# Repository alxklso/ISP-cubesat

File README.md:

# ISP-cubesat
This is the repo for the Isomer Space Program (ISP) 1U CoyoteSat CubeSat mission.

This repo contains:
- [mainboard-v05]: PyCubed V5 Mainboard  
- [batt-board]: PyCubed V1b Battery Board
- [software]: PyCubed Flight Software  
- [cosmic-watch]: Cosmic Watch (payload)
- [solar-panels]: Solar Panel PCBs
- [antenna]: Antenna PCBs
- [bottom-adapter]: Bottom adapter plate w/ solar cells
- [ISP.pretty]: Custom KiCad footprint library
- [datasheets]: Datasheets for components 
- [firmware]: Firmware for PyCubed V5 board
- [pics]: Progress pics of the CubeSat

Visit our website to learn more: [ISP Website](https://isomer.space)

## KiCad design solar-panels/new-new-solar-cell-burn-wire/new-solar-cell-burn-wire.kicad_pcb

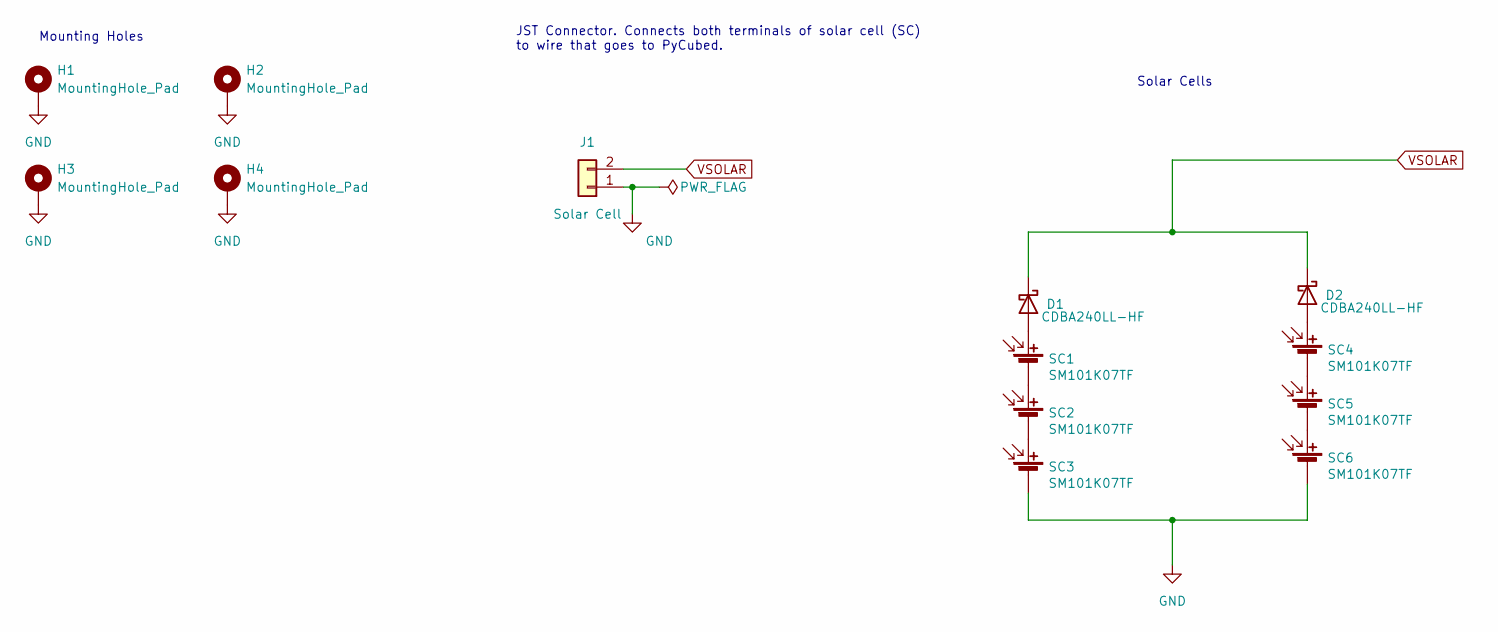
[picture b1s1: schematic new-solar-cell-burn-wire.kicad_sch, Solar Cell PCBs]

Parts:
D1, D2: CDBA240LL-HF; DO-214AC
H1, H2, H3, H4: MountingHole_Pad; MountingHole_3.2mm_M3_DIN965_Pad
J1: Solar Cell; 2053380002
SC1, SC2, SC3, SC4, SC5, SC6: SM101K07TF

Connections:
GND: H1.1, H2.1, H3.1, H4.1, J1.1, SC3.2 (-), SC6.2 (-)
unnamed: D1.2 (A), SC1.1 (+)
unnamed: D2.2 (A), SC4.1 (+)
unnamed: SC1.2 (-), SC2.1 (+)
unnamed: SC2.2 (-), SC3.1 (+)
unnamed: SC4.2 (-), SC5.1 (+)
unnamed: SC5.2 (-), SC6.1 (+)
VSOLAR: D1.1 (K), D2.1 (K), J1.2

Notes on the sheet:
Mounting Holes
Solar Cells
JST Connector. Connects both terminals of solar cell (SC) to wire that goes to PyCubed.

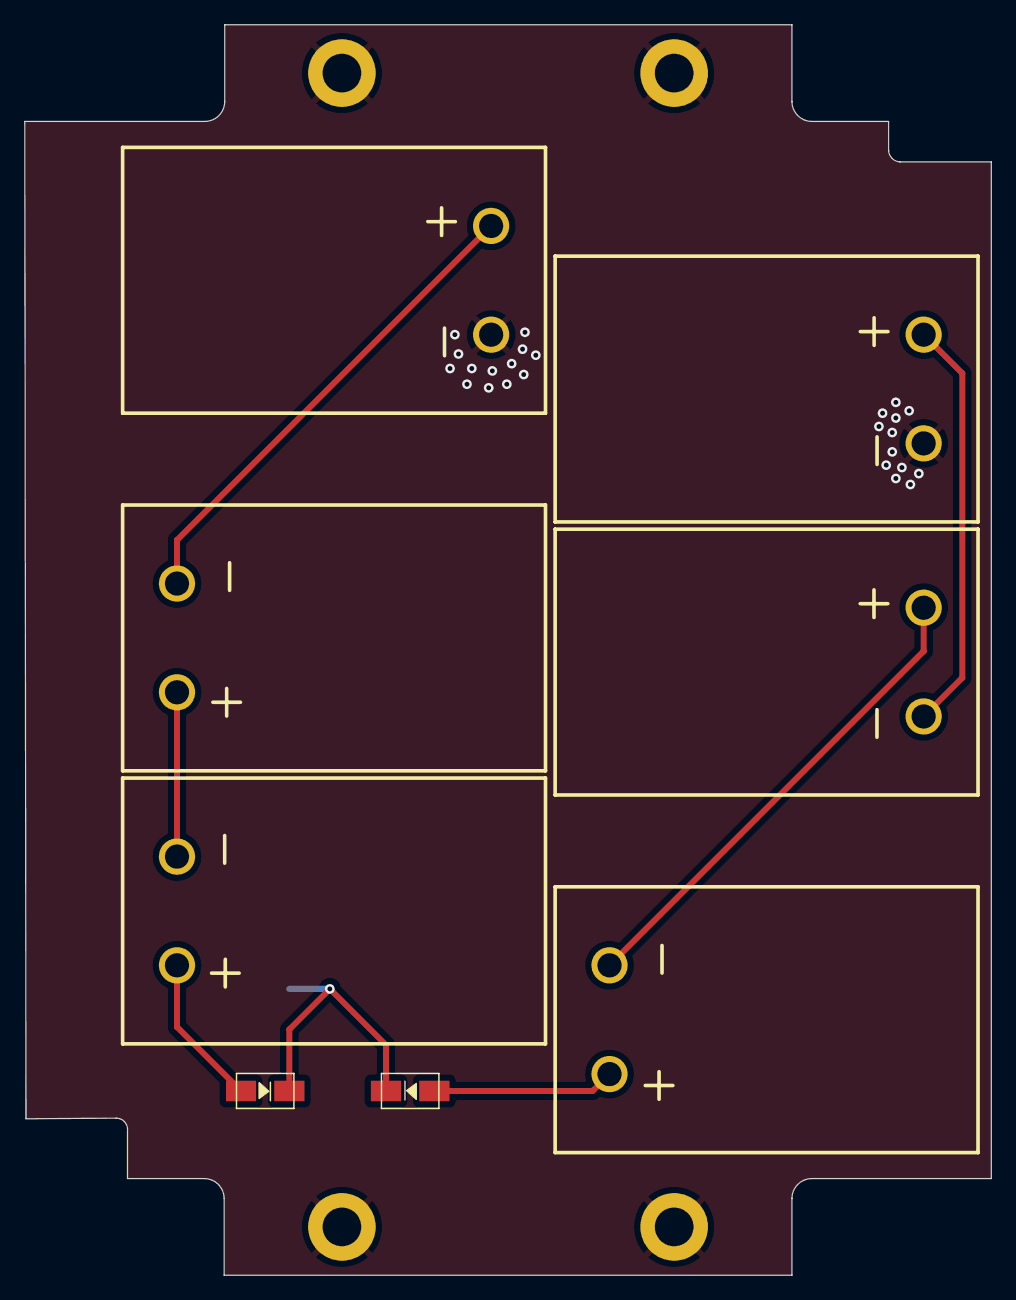
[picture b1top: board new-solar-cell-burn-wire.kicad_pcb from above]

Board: 2 copper layers, 80.0 x 103.5 mm, 13 parts (1 on the bottom side), 8 nets.

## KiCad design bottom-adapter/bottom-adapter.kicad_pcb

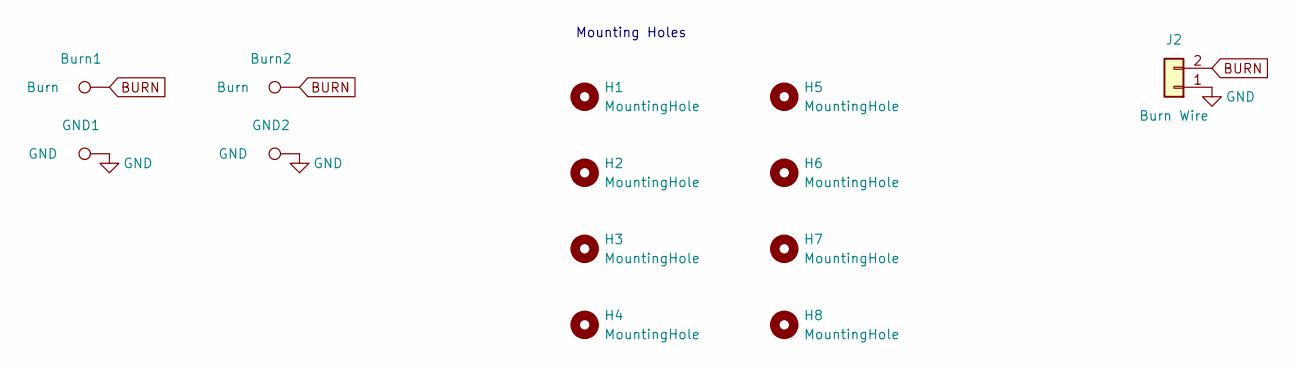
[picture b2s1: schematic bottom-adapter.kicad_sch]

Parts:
Burn1, Burn2: Burn; TestPoint_THTPad_2.0x2.0mm_Drill1.0mm
GND1, GND2: GND; TestPoint_THTPad_2.0x2.0mm_Drill1.0mm
H1, H2, H3, H4: MountingHole; MountingHole_3.7mm_Pad_Modified
H5, H6, H7, H8: MountingHole; MountingHole_2.7mm_M2.5_DIN965_Pad
J2: Burn Wire; pico_lock_2mm_2circuit

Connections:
BURN: Burn1.1, Burn2.1, J2.2
GND: GND1.1, GND2.1, J2.1

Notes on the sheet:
Mounting Holes

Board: 2 copper layers, 14 parts (1 on the bottom side), 2 nets, no tracks yet.

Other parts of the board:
G: LOGO

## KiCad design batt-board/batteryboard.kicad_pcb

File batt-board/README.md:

# PyCubed Battery Board 🔋

## [⭐ See the PyCubed Battery page for more details](https://www.notion.so/maholli/PyCubed-4cbfac7e9b684852a2ab2193bd485c4d)

2S2P Li-ion battery pack for CubeSat designs.
   - Fits 18650 cells (like the LG INR18650-MJ1)
   - Meets maximum capacity requirements of common CubeSat integrators
   - Uses components with radiation testing heritage
      - R5460x2xx for protection against
         - over-charge 
         - over-discharge
         - short-circuit
         - excess discharge-current
         - excess charge-current

## Interactive Bill of Materials 🛒
- [batteryboard-v01](https://pycubed.github.io/hardware/batteryboard-v01)

This board is merely a starting point for your spacecraft. Always follow the requirements set forth by your launch provider and integrator.

<br>
<br>
<br>
<br />This work is licensed under a <a rel="license" href="http://creativecommons.org/licenses/by/4.0/">Creative Commons Attribution 4.0 International License</a>.

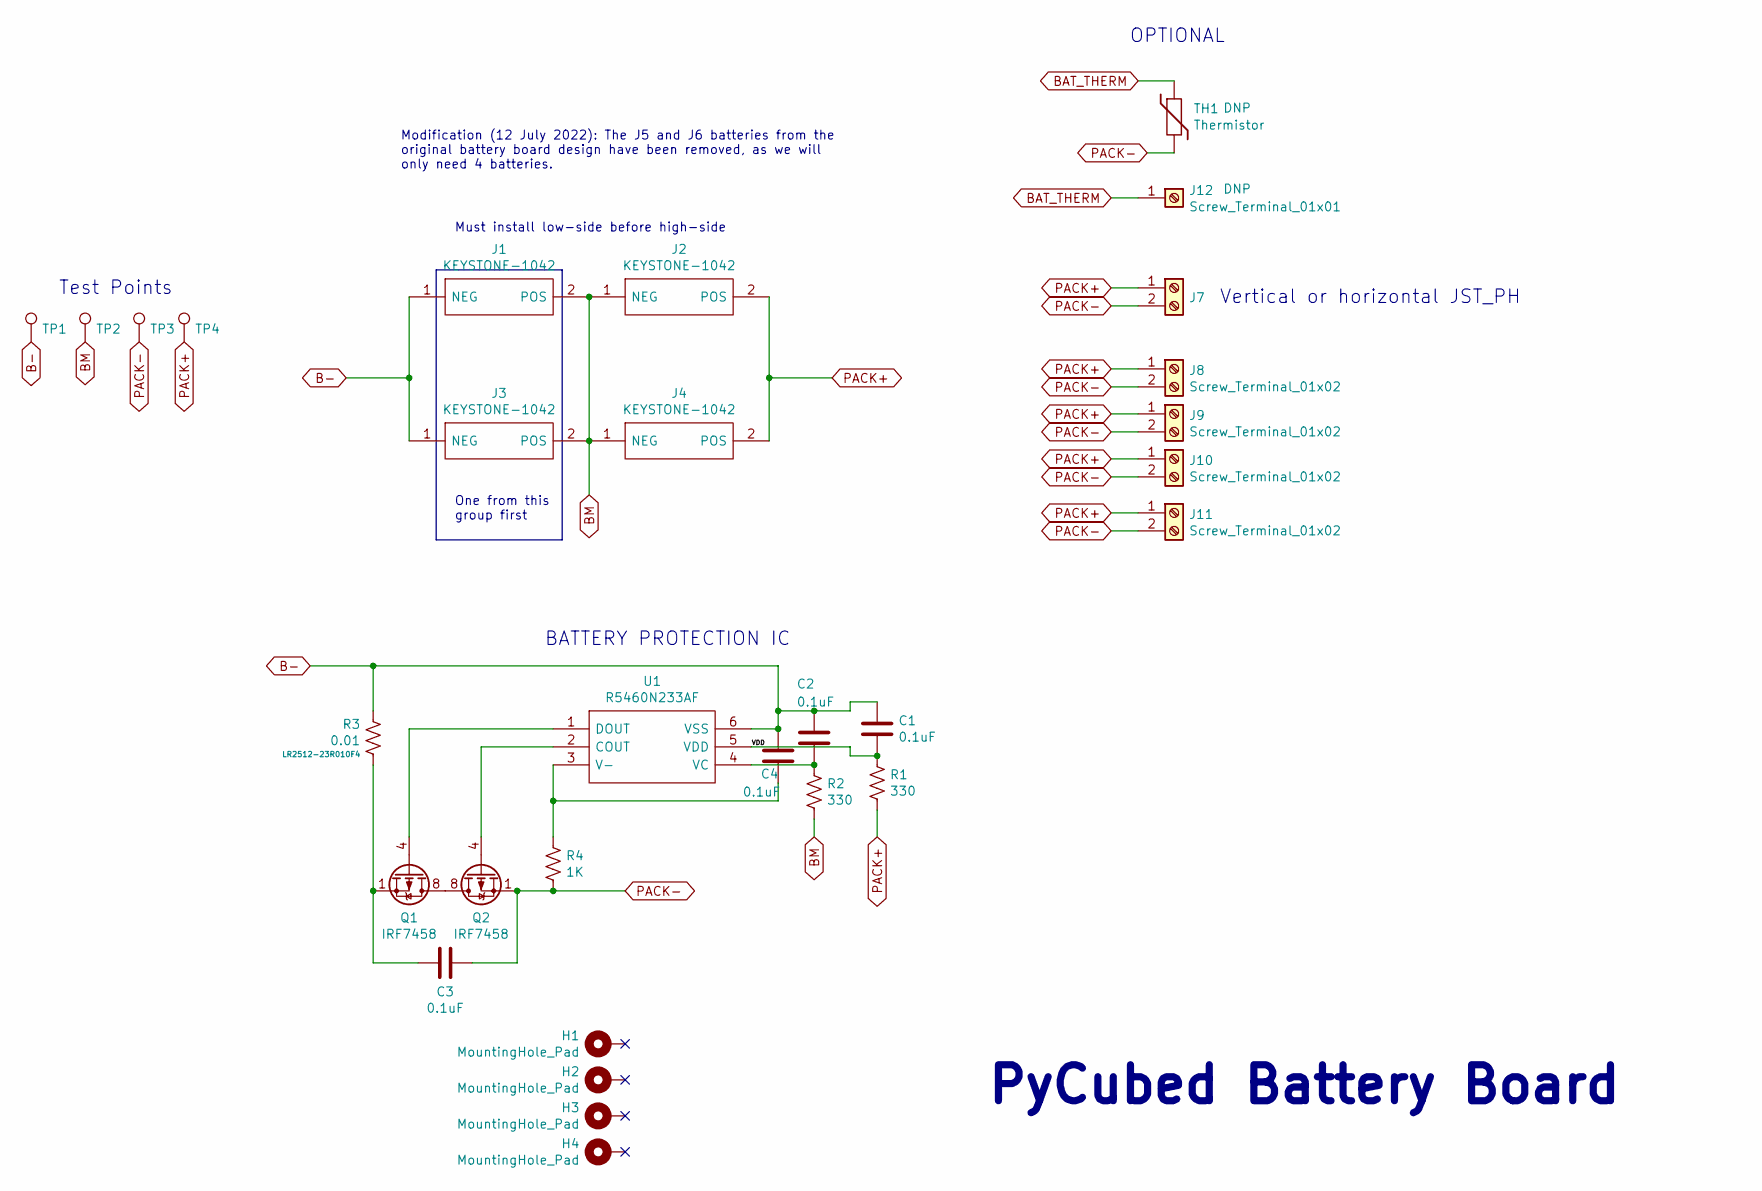
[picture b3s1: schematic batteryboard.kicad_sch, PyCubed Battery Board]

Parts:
C1, C2, C3, C4: 0.1uF; C_0603_1608Metric
H1, H2, H3, H4: MountingHole_Pad; MountingHole_3.2mm_M3_DIN965_PadMOD
J1, J2, J3, J4: KEYSTONE-1042; Manufacturer_Part_Number 1042; Mouser Part Number 534-1042
J7: JST_PH_S2B-PH-SM4; JST_PH_S2B-PH-SM4-TB_1x02-1MP_P2.00mm_Horizontal
J8, J9, J10, J11: Screw_Terminal_01x02; SCREWTERMINAL-3.5MM-2_LOCK
J12: Screw_Terminal_01x01; PinHeader_1x01_P1.00mm_Vertical
Q1, Q2: IRF7458; SOIC-8_3.9x4.9mm_P1.27mm
R1, R2: 330; R_0603_1608Metric
R3: 0.01; R_2512_6332Metric
R4: 1K; R_0603_1608Metric; Manufacturer_Part_Number LR2512-23R010F4
TH1: Thermistor; R_Axial_DIN0204_L3.6mm_D1.6mm_P5.08mm_Vertical
TP1, TP2, TP3, TP4: TestPoint; TestPoint_Loop_D1.80mm_Drill1.0mm_Beaded
U1: R5460N233AF; SOT95P280X130-6N; Manufacturer_Part_Number R5460N233AF-TR-FE; Mouser Part Number 848-R5460N233AFTRFE

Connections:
/VDD: C1.2, R1.2, U1.5 (VDD)
B-: C1.1, C2.1, C4.1, J1.1 (NEG), J3.1 (NEG), R3.1, TP1.1, U1.6 (VSS)
BAT_THERM: J12.1, TH1.1
BM: J1.2 (POS), J2.1 (NEG), J3.2 (POS), J4.1 (NEG), R2.1, TP2.1
unnamed: C2.2, R2.2, U1.4 (VC)
unnamed: C3.1, Q1.1 (S), Q1.2 (S), Q1.3 (S), R3.2
unnamed: C4.2, R4.1, U1.3 (V-)
unnamed: Q1.4 (G), U1.1 (DOUT)
unnamed: Q1.5 (D), Q1.6 (D), Q1.7 (D), Q1.8 (D), Q2.5 (D), Q2.6 (D), Q2.7 (D), Q2.8 (D)
unnamed: Q2.4 (G), U1.2 (COUT)
PACK+: J2.2 (POS), J4.2 (POS), J7.1, J8.1, J9.1, J10.1, J11.1, R1.1, TP4.1
PACK-: C3.2, J7.2, J8.2, J9.2, J10.2, J11.2, Q2.1 (S), Q2.2 (S), Q2.3 (S), R4.2, TH1.2, TP3.1

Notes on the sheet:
BATTERY PROTECTION IC
One from this group first
Test Points
Modification (12 July 2022): The J5 and J6 batteries from the original battery board design have been removed, as we will only need 4 batteries.
Must install low-side before high-side
Vertical or horizontal JST_PH
PyCubed Battery Board
OPTIONAL

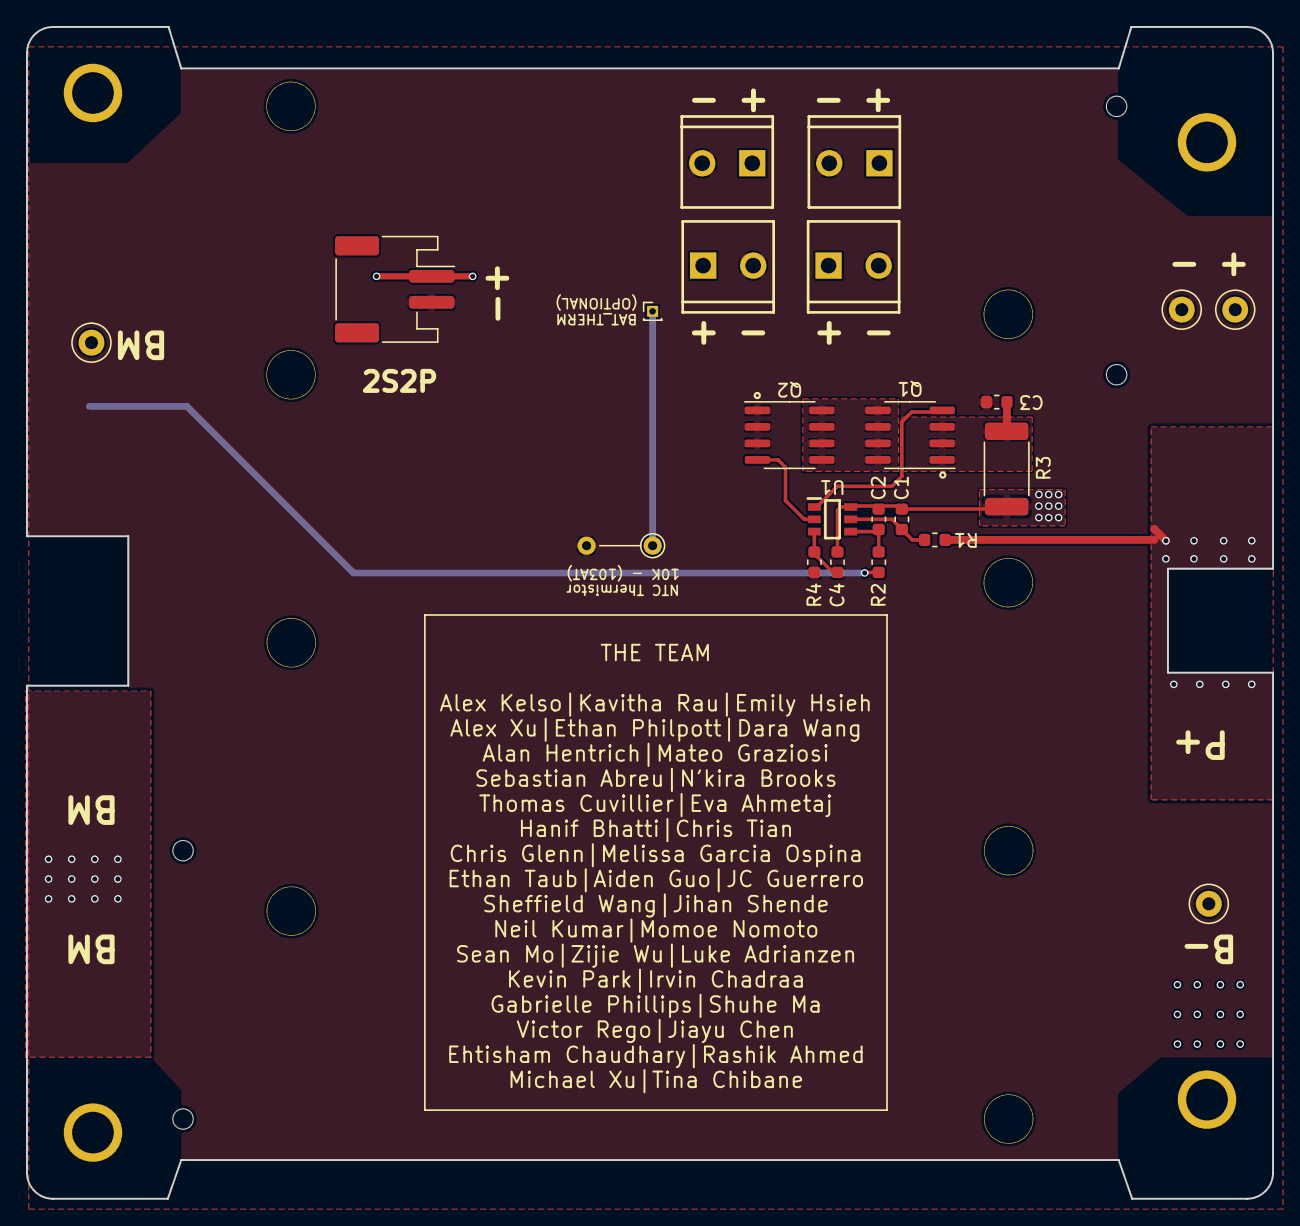
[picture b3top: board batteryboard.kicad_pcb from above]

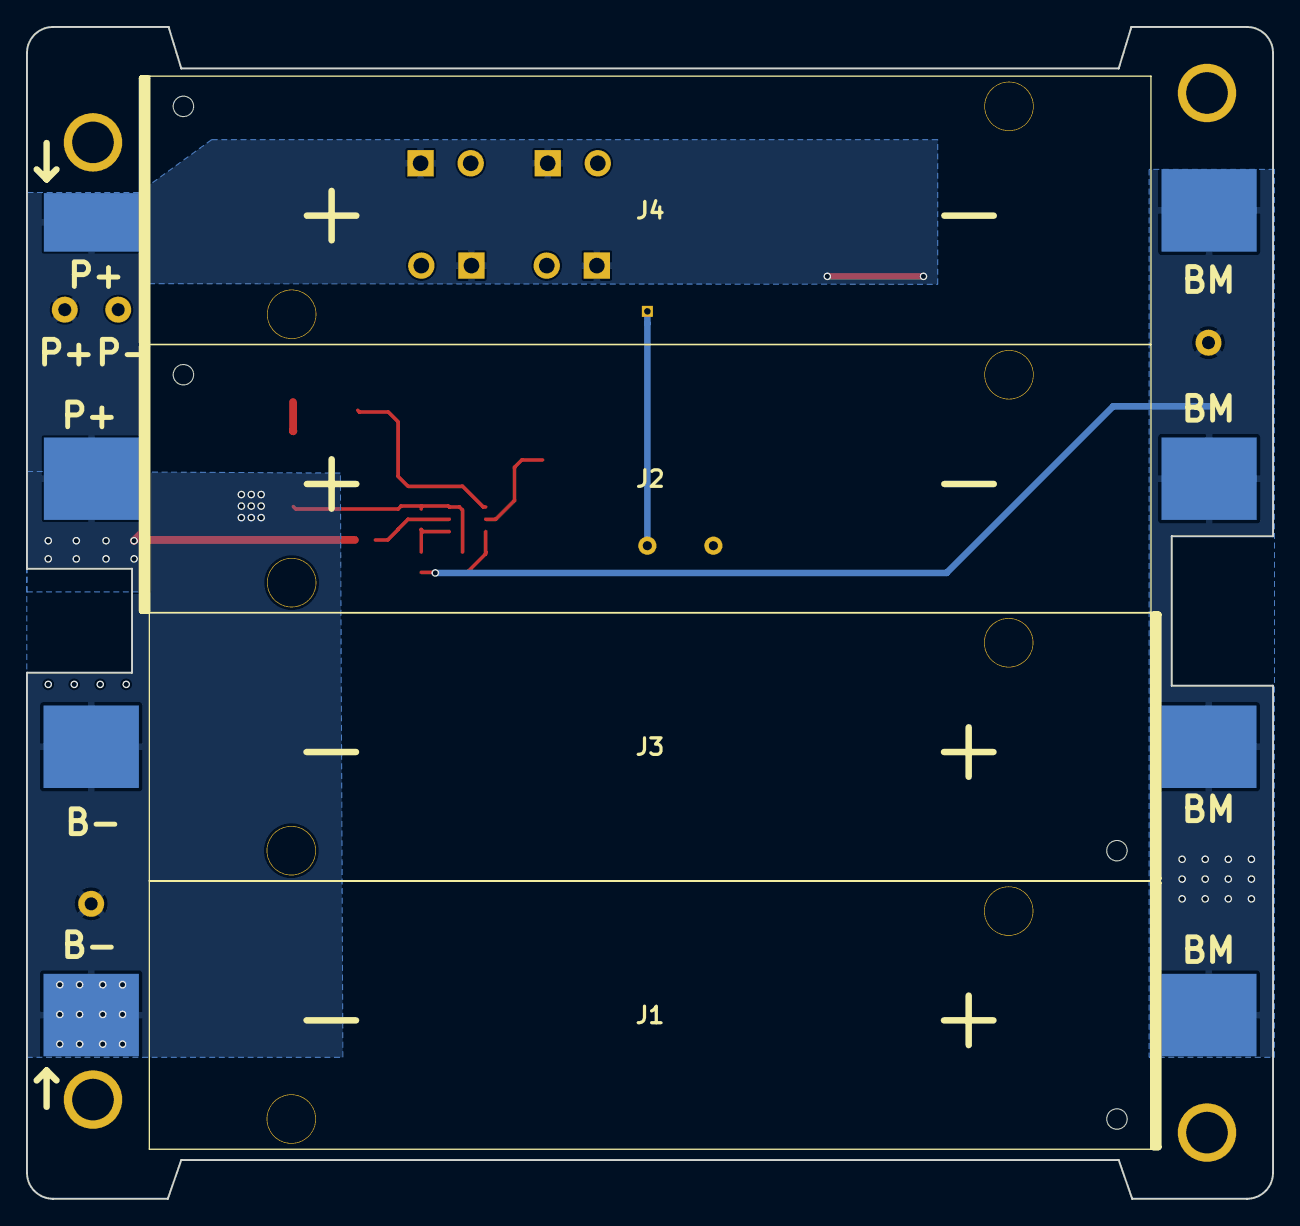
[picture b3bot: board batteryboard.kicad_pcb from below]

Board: 2 copper layers, 95.9 x 90.2 mm, 30 parts (4 on the bottom side), 12 nets.

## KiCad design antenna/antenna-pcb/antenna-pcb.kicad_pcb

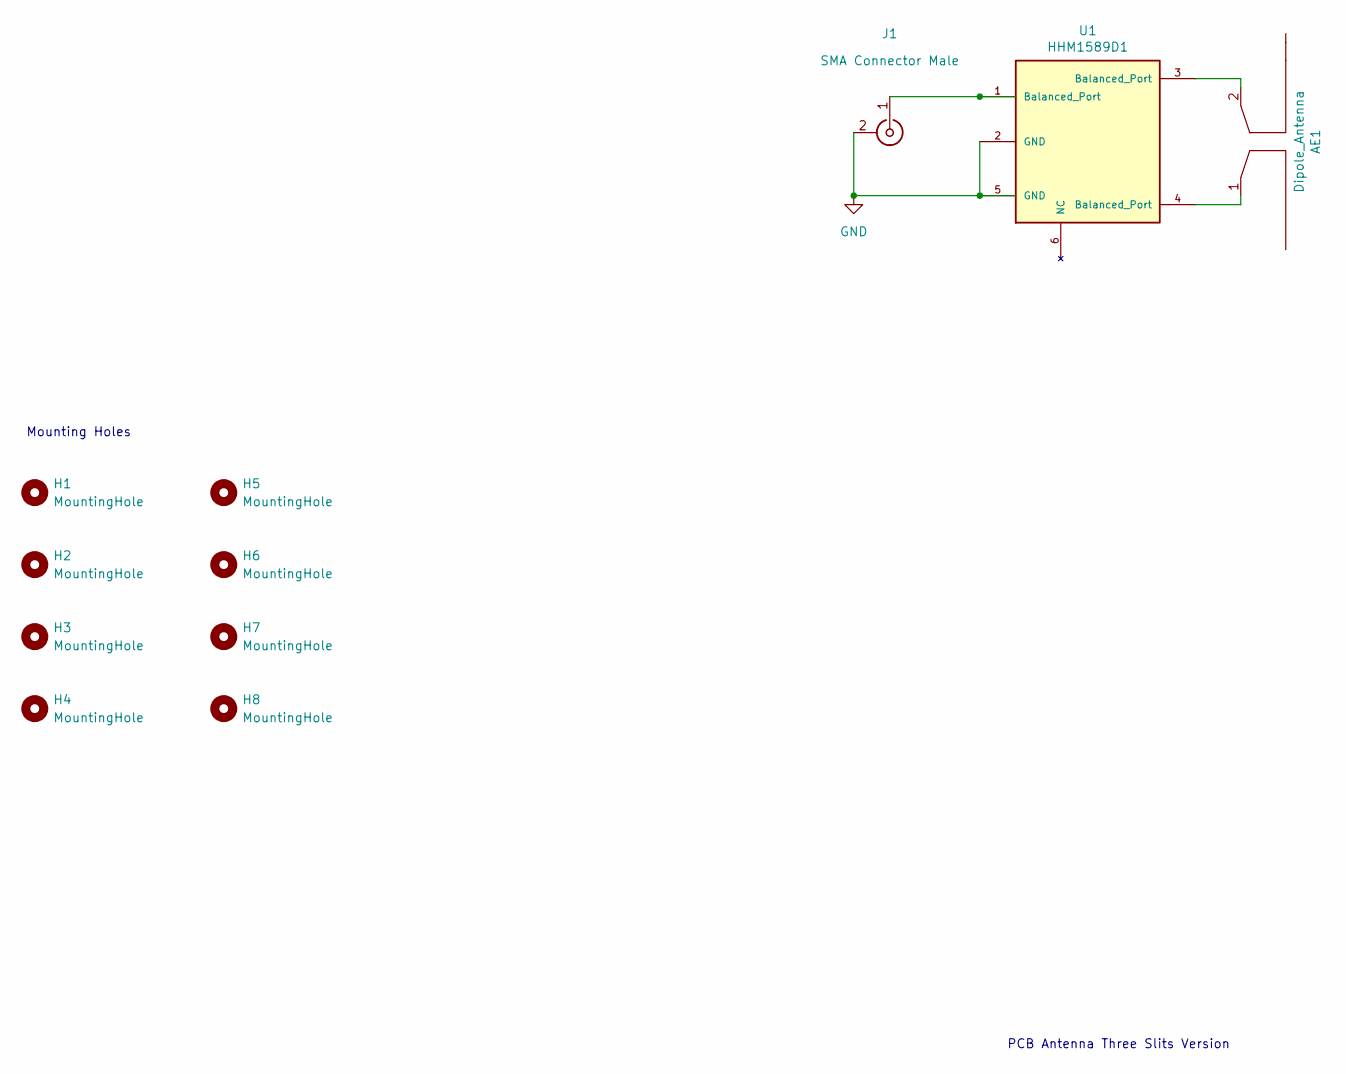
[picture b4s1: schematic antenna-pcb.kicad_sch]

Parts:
AE1: Dipole_Antenna; Antenna_Pads
H1, H2, H3, H4: MountingHole; MountingHole_3.7mm_Pad_Modified
H5, H6, H7, H8: MountingHole; MountingHole_2.7mm_M2.5_DIN965_Pad
J1: SMA Connector Male; SMA_Connector
U1: HHM1589D1; Balun_Johanson_5400BL15B050E

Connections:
GND: J1.2 (Ext), U1.2 (GND), U1.5 (GND)
unnamed: J1.1 (In), U1.1 (Balanced_Port)
unnamed: AE1.2, U1.3 (Balanced_Port)
unnamed: AE1.1, U1.4 (Balanced_Port)

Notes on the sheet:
Mounting Holes
PCB Antenna Three Slits Version

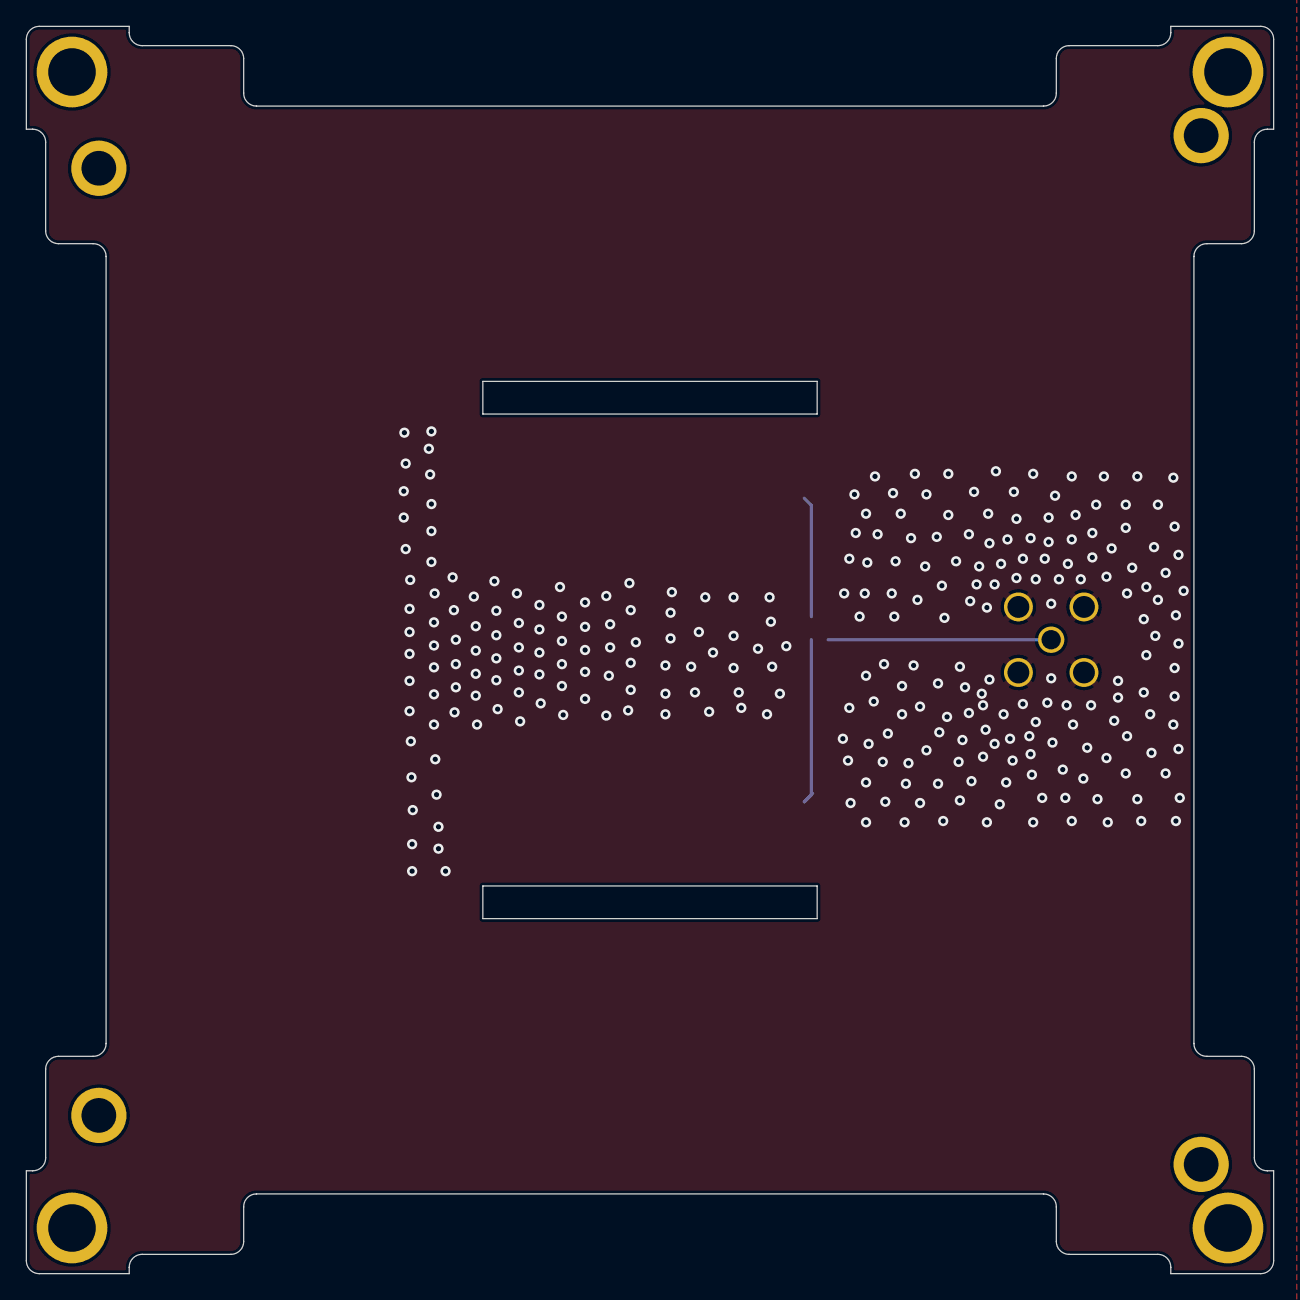
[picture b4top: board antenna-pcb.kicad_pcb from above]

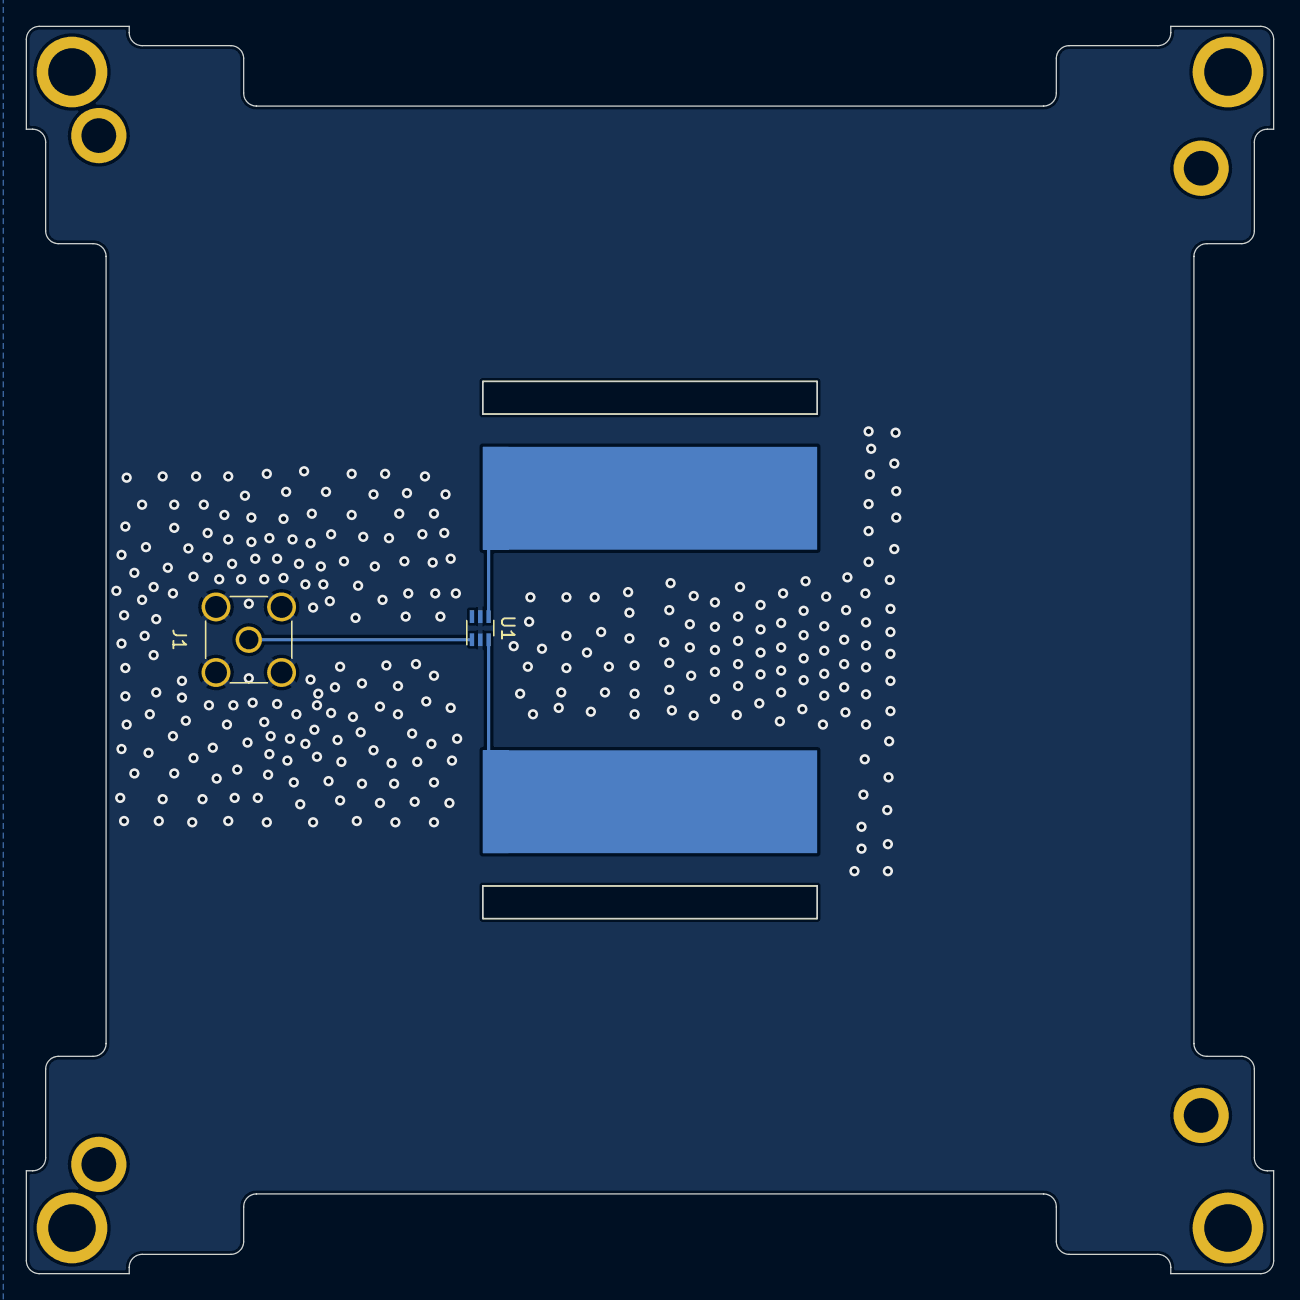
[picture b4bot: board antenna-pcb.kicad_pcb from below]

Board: 2 copper layers, 97.0 x 97.0 mm, 11 parts (3 on the bottom side), 4 nets.

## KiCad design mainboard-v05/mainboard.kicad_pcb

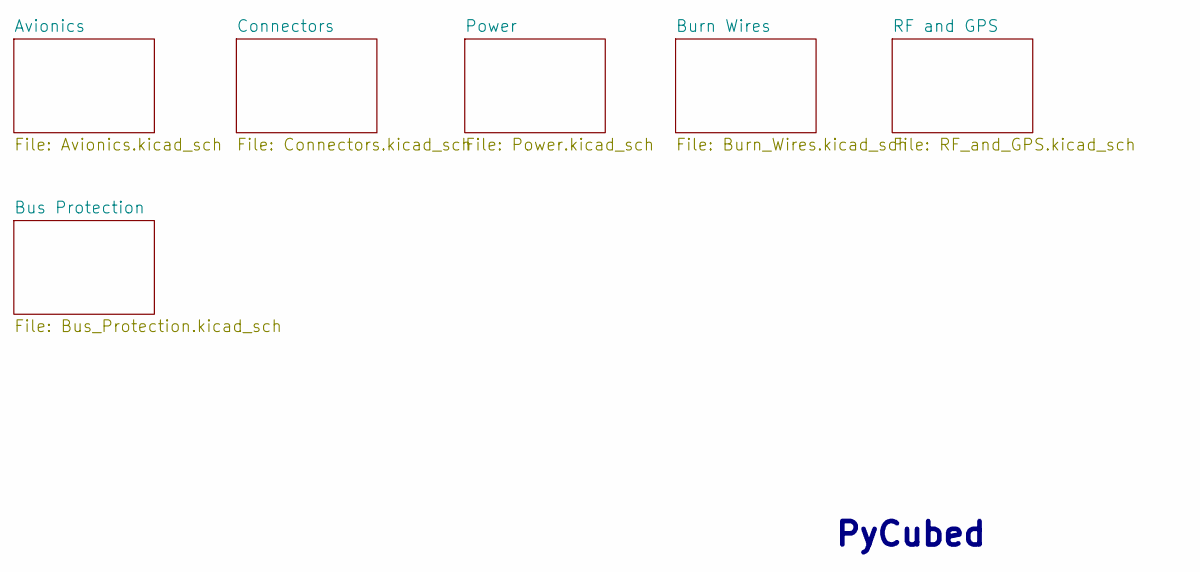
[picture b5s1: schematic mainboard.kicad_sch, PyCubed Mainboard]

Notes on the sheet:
PyCubed

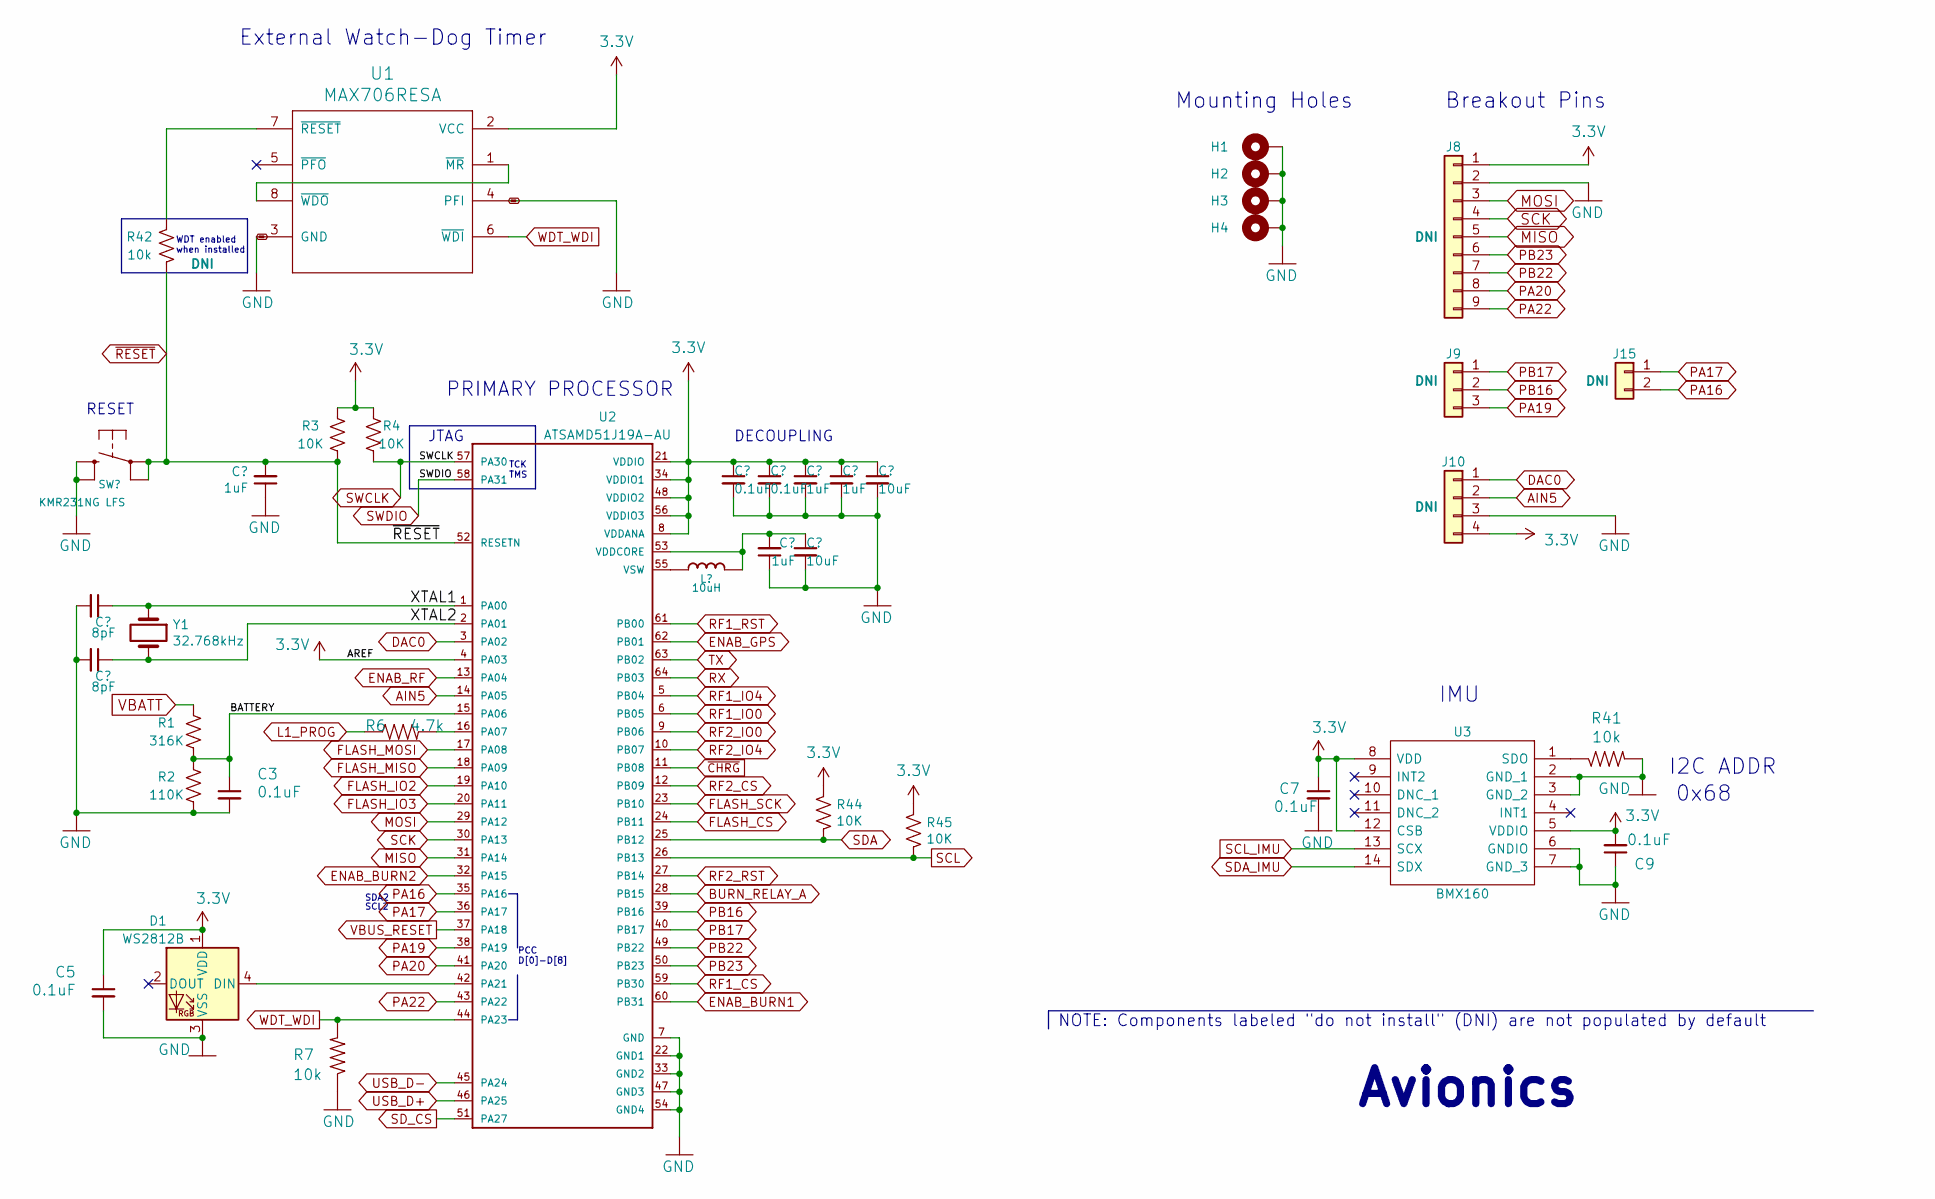
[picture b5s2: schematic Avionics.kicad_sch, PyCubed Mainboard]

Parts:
C1, C2: 8pF; C_0603_1608Metric
C3, C5, C7, C9, C10, C11: 0.1uF; C_0603_1608Metric
C4, C12, C13, C15: 1uF; C_0603_1608Metric
C14, C16: 10uF; C_0603_1608Metric
D1: WS2812B; LED_WS2812B_PLCC4_5.0x5.0mm_P3.2mm; Manufacturer_Part_Number WS2812B-B
H1, H2, H3, H4: MountingHole_Pad; MountingHole_3.2mm_M3_DIN965_Pad
J8: Conn_01x09; PinHeader_1x09_P2.54mm_Vertical
J9: Conn_01x03; PinHeader_1x03_P2.54mm_Vertical
J10: Conn_01x04; PinHeader_1x04_P2.54mm_Vertical
J15: Conn_01x02; PinHeader_CUSTOM3
L1: 10uH; L_0805_2012Metric_Pad1.15x1.40mm_HandSolder; Manufacturer_Part_Number MGFL2012F100MT-LF
R1: 316K; R_0603_1608Metric
R2: 110K; R_0603_1608Metric
R3, R4, R44, R45: 10K; R_0603_1608Metric
R6: 4.7k; R_0603_1608Metric
R7, R41, R42: 10k; R_0603_1608Metric
SW1: KMR231NG LFS; BTN_KMR2_4.6X2.8; Manufacturer_Part_Number KMR231NG LFS
U1: MAX706RESA; SO-8_3.9x4.9mm_P1.27mm; Manufacturer_Part_Number MAX706RESA
U2: ATSAMD51J19A-AU; QFP50P1200X1200X120-64N; Manufacturer_Part_Number ATSAMD51J19A-AU
U3: BMX160; Manufacturer_Part_Number BMX160
Y1: 32.768kHz; Crystal_SMD_3215-2Pin_3.2x1.5mm; Manufacturer_Part_Number SC-32S32.768kHz20PPM7pF

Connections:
3.3V: C5.1, C7.1, C9.2, C10.1, C11.1, C13.1, C15.1, C16.1, D1.1 (VDD), J8.1, J10.4, R3.1, R4.1, R44.1, R45.1, U1.2 (VCC), U2.4 (PA03), U2.8 (VDDANA), U2.21 (VDDIO), U2.34 (VDDIO1), U2.48 (VDDIO2), U2.56 (VDDIO3), U3.5 (VDDIO), U3.8 (VDD), U3.12 (CSB); also elsewhere on the board
/Avionics/BATTERY: C3.1, R1.2, R2.2, U2.15 (PA06)
/Avionics/XTAL1: C1.1, U2.1 (PA00), Y1.1
/Avionics/XTAL2: C2.1, U2.2 (PA01), Y1.2
AIN5: J10.2, U2.14 (PA05)
BURN_RELAY_A: U2.28 (PB15); also elsewhere on the board
DAC0: J10.1, U2.3 (PA02)
ENAB_BURN1: U2.60 (PB31); also elsewhere on the board
ENAB_BURN2: U2.32 (PA15); also elsewhere on the board
ENAB_GPS: U2.62 (PB01); also elsewhere on the board
ENAB_RF: U2.13 (PA04); also elsewhere on the board
FLASH_CS: U2.24 (PB11); also elsewhere on the board
FLASH_IO2: U2.19 (PA10); also elsewhere on the board
FLASH_IO3: U2.20 (PA11); also elsewhere on the board
FLASH_MISO: U2.18 (PA09); also elsewhere on the board
FLASH_MOSI: U2.17 (PA08); also elsewhere on the board
FLASH_SCK: U2.23 (PB10); also elsewhere on the board
GND: C1.2, C2.2, C3.2, C4.1, C5.2, C7.2, C9.1, C10.2, C11.2, C12.1, C13.2, C14.2, C15.2, C16.2, D1.3 (VSS), H1.1, H2.1, H3.1, H4.1, J8.2, J10.3, R2.1, R7.1, R41.2, SW1.B (S), SW1.B' (S1), U1.3 (GND), U1.4 (PFI), U2.7 (GND), U2.22 (GND1), U2.33 (GND2), U2.47 (GND3), U2.54 (GND4), U3.2 (GND_1), U3.3 (GND_2), U3.6 (GNDIO), U3.7 (GND_3); also elsewhere on the board
L1_PROG: R6.1; also elsewhere on the board
MISO: J8.5, U2.31 (PA14); also elsewhere on the board
MOSI: J8.3, U2.29 (PA12); also elsewhere on the board
unnamed: C12.2, C14.1, L1.1, U2.53 (VDDCORE)
unnamed: D1.4 (DIN), U2.42 (PA21)
unnamed: L1.2, U2.55 (VSW)
unnamed: R6.2, U2.16 (PA07)
unnamed: R41.1, U3.1 (SDO)
unnamed: R42.2, U1.7 (~RESET)
unnamed: U1.1 (~MR), U1.8 (~WDO)
PA16: J15.2, U2.35 (PA16); also elsewhere on the board
PA17: J15.1, U2.36 (PA17); also elsewhere on the board
PA19: J9.3, U2.38 (PA19); also elsewhere on the board
PA20: J8.8, U2.41 (PA20); also elsewhere on the board
PA22: J8.9, U2.43 (PA22); also elsewhere on the board
PB16: J9.2, U2.39 (PB16); also elsewhere on the board
PB17: J9.1, U2.40 (PB17); also elsewhere on the board
PB22: J8.7, U2.49 (PB22); also elsewhere on the board
PB23: J8.6, U2.50 (PB23); also elsewhere on the board
RF1_CS: U2.59 (PB30); also elsewhere on the board
RF1_IO0: U2.6 (PB05); also elsewhere on the board
RF1_IO4: U2.5 (PB04); also elsewhere on the board
RF1_RST: U2.61 (PB00); also elsewhere on the board
RF2_CS: U2.12 (PB09); also elsewhere on the board
RF2_IO0: U2.9 (PB06); also elsewhere on the board
RF2_IO4: U2.10 (PB07); also elsewhere on the board
RF2_RST: U2.27 (PB14); also elsewhere on the board
RX: U2.64 (PB03); also elsewhere on the board
SCK: J8.4, U2.30 (PA13); also elsewhere on the board
SCL: R45.2, U2.26 (PB13); also elsewhere on the board
SCL_IMU: U3.13 (SCX); also elsewhere on the board
SDA: R44.2, U2.25 (PB12); also elsewhere on the board
SDA_IMU: U3.14 (SDX); also elsewhere on the board
SD_CS: U2.51 (PA27); also elsewhere on the board
SWCLK: R4.2, U2.57 (PA30); also elsewhere on the board
SWDIO: U2.58 (PA31); also elsewhere on the board
TX: U2.63 (PB02); also elsewhere on the board
USB_D+: U2.46 (PA25); also elsewhere on the board
USB_D-: U2.45 (PA24); also elsewhere on the board
VBATT: R1.1; also elsewhere on the board
VBUS_RESET: U2.37 (PA18); also elsewhere on the board
WDT_WDI: R7.2, U1.6 (~WDI), U2.44 (PA23)
~CHRG: U2.11 (PB08); also elsewhere on the board
~RESET: C4.2, R3.2, R42.1, SW1.A, SW1.A' (P1), U2.52 (RESETN); also elsewhere on the board

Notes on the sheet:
I2C ADDR
0x68
WDT enabled when installed
Breakout Pins
PRIMARY PROCESSOR
NOTE: Components labeled "do not install" (DNI) are not populated by default
TCK TMS
SDA2
Avionics
RESET
DECOUPLING
Mounting Holes
IMU
External Watch-Dog Timer
SCL2
PCC D[0]-D[8]
JTAG

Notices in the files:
parts and their libraries:
Copyright 2021 Accelerated Designs. All rights reserved.
Copyright 2016 Accelerated Designs. All rights reserved.
